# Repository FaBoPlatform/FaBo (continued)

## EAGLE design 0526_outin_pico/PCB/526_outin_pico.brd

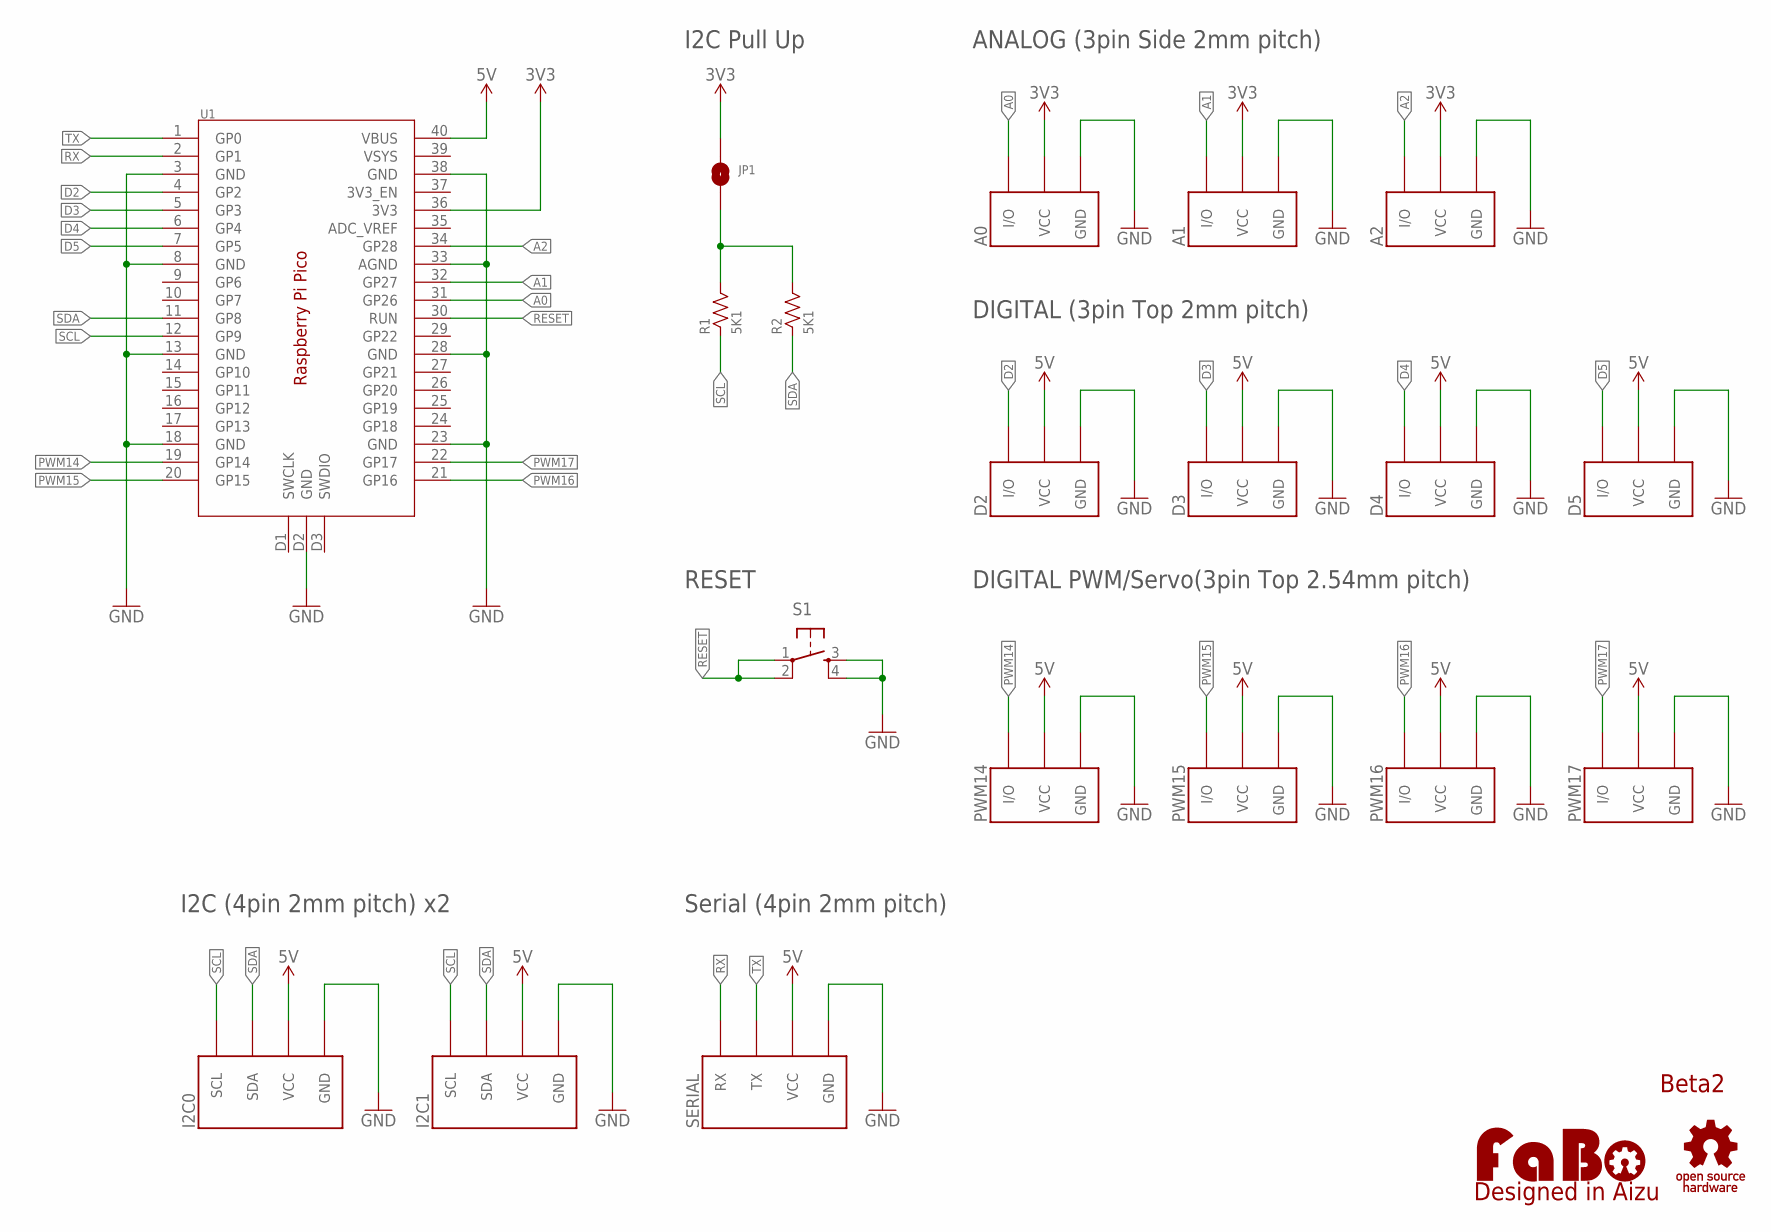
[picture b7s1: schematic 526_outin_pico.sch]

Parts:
A0, A1, A2: FABO_BRICK_3PIN-S03B-PASK-2_LONG; FABO_BRICK_3PIN_S03B-PASK-2_LONG
D2, D3, D4, D5: FABO_BRICK_3PIN-B03B-PASK-1; FABO_BRICK_3PIN_B03B-PASK-1
I2C0, I2C1: FABO_BRICK_I2C-B04B-PASK-1; FABO_BRICK_I2C_B04B-PASK-1
JP1: SMD-JUMPER-2_SHORT; SMD-JUMPER-2-SHORT
LOGO1: LOGO_OSHW-M_BOTTOM; LOGO_OSHW_M_BOTTOM
LOGO2: LOGO_FABO-M; LOGO_FABO_M
PWM14, PWM15, PWM16, PWM17: FABO_BRICK_3PIN-HEADER; FABO_BRICK_3PIN_HEADER
R1, R2: 5K1; 0603
S1: TACT-SWITCH-6MM; DTS_6_V
SERIAL: FABO_BRICK_SERIAL-B04B-PASK-1; FABO_BRICK_SERIAL_B04B-PASK-1
U1: RASPBERRY_PI_PICO; RASPBERRY_PI_PICO_SMD

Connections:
3V3: A0.VCC, A1.VCC, A2.VCC, JP1.1, U1.36 (3V3)
5V: D2.VCC, D3.VCC, D4.VCC, D5.VCC, I2C0.VCC, I2C1.VCC, PWM14.VCC, PWM15.VCC, PWM16.VCC, PWM17.VCC, SERIAL.VCC, U1.40 (VBUS)
A0: A0.I/O, U1.31 (GP26)
A1: A1.I/O, U1.32 (GP27)
A2: A2.I/O, U1.34 (GP28)
D2: D2.I/O, U1.4 (GP2)
D3: D3.I/O, U1.5 (GP3)
D4: D4.I/O, U1.6 (GP4)
D5: D5.I/O, U1.7 (GP5)
GND: A0.GND, A1.GND, A2.GND, D2.GND, D3.GND, D4.GND, D5.GND, I2C0.GND, I2C1.GND, PWM14.GND, PWM15.GND, PWM16.GND, PWM17.GND, S1.3, S1.4, SERIAL.GND, U1.3 (GND), U1.8 (GND), U1.13 (GND), U1.18 (GND), U1.23 (GND), U1.28 (GND), U1.33 (AGND), U1.38 (GND), U1.D2 (GND)
unnamed: JP1.2, R1.2, R2.2
PWM14: PWM14.I/O, U1.19 (GP14)
PWM15: PWM15.I/O, U1.20 (GP15)
PWM16: PWM16.I/O, U1.21 (GP16)
PWM17: PWM17.I/O, U1.22 (GP17)
RESET: S1.1, S1.2, U1.30 (RUN)
RX: SERIAL.RX, U1.2 (GP1)
SCL: I2C0.SCL, I2C1.SCL, R1.1, U1.12 (GP9)
SDA: I2C0.SDA, I2C1.SDA, R2.1, U1.11 (GP8)
TX: SERIAL.TX, U1.1 (GP0)

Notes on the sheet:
Beta2
DIGITAL (3pin Top 2mm pitch)
ANALOG (3pin Side 2mm pitch)
DIGITAL PWM/Servo(3pin Top 2.54mm pitch)
I2C (4pin 2mm pitch) x2
Serial (4pin 2mm pitch)
RESET
I2C Pull Up

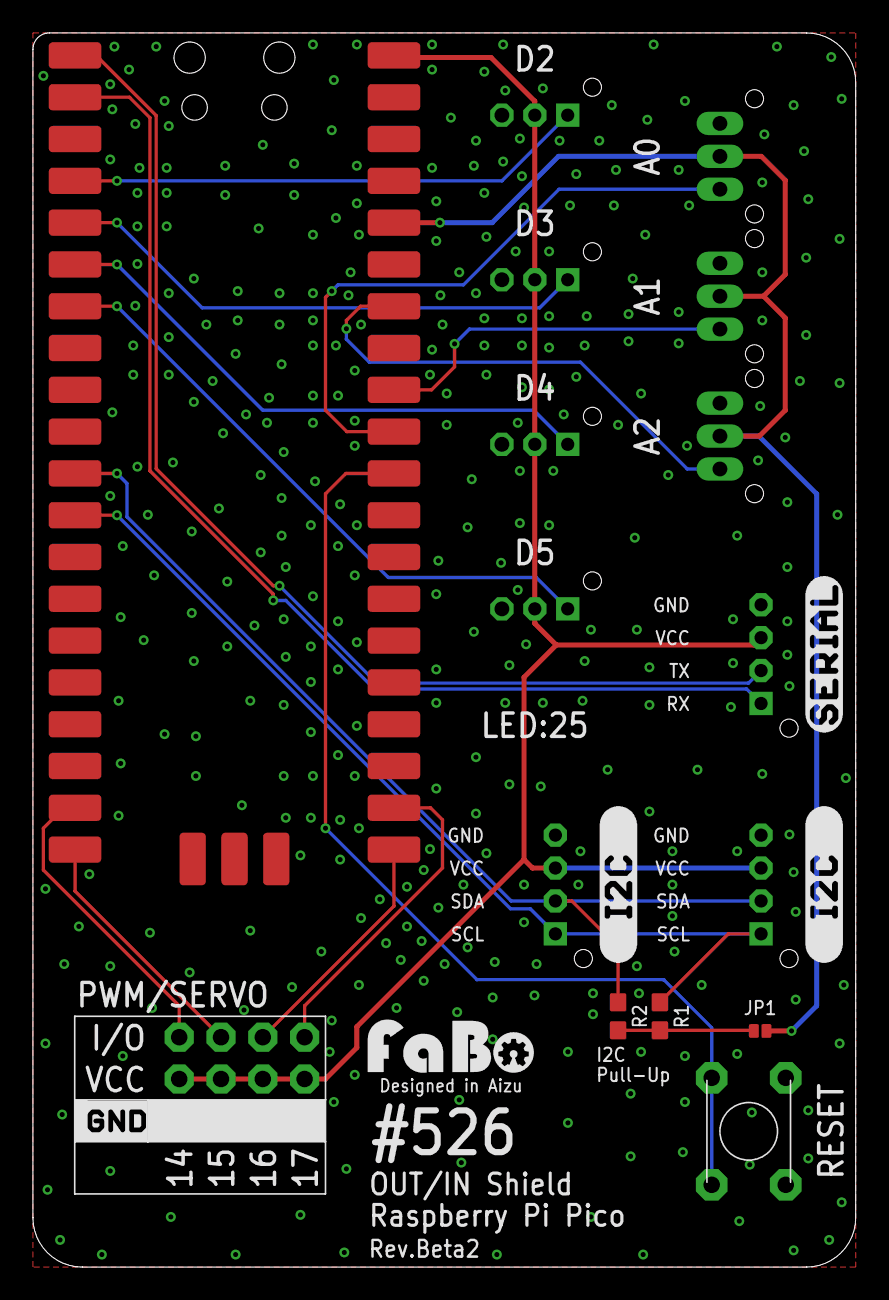
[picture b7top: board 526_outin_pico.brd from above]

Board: 2 copper layers, 50.0 x 75.0 mm, 25 parts (0 on the bottom side), 20 nets.

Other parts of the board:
U$2: LOGO_SILK_SERIAL2
U$11, U$12: LOGO_SILK_I2C
U$19: LOGO_SILK_GND

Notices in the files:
parts and their libraries:
FaBo-Template: Released under the Creative Commons Attribution-ShareAlike 4.0 License
https://creativecommons.org/licenses/by-sa/4.0
FaBo-Symbol: Released under the Creative Commons
